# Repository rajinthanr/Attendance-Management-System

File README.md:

# Card Attendance System

A battery-powered NFC attendance logger. A student taps an ID card and the unit
confirms the tap with an LED and a vibration pulse, and stores the card number
with a timestamp in on-chip flash. Plugged into a PC over USB-C, it appears as a
USB drive, with no driver needed.

A desktop companion app for the PC keeps the student names, decides which cards
are registered and works out who attended which lecture.

The repository holds the hardware (KiCad 10), the firmware (STM32CubeIDE /
Makefile), the companion app (Python, Qt) and a 3D-printable enclosure.

## Install the companion app on Windows

1. Download the installer:
   [`Companion/dist/AttendanceLogger-Setup-1.0.0.exe`](Companion/dist/AttendanceLogger-Setup-1.0.0.exe)
   ([direct download](https://github.com/rajinthanr/attendance-management-system/raw/main/Companion/dist/AttendanceLogger-Setup-1.0.0.exe), 26 MB).
2. Run it. It installs for the current user without an admin prompt (it offers
   an all-users install too), into `%LOCALAPPDATA%\Programs\Attendance Logger`.
   Python and Qt are bundled, so nothing else needs installing.
3. Start **Attendance Logger** from the Start menu (or the optional desktop
   icon). **Attendance Logger (demo, made-up data)** shows the whole app without
   a device.

- **Requirements:** 64-bit Windows 10 or 11.
- **"Windows protected your PC":** the installer is not code-signed, so
  SmartScreen may warn the first time. Choose *More info*, then *Run anyway*.
- **Your data** lives in `%USERPROFILE%\AttendanceLogger\attendance.db`, with a
  daily backup in `backups\` (the last 14 kept). Uninstalling or upgrading the
  app leaves it in place.
- **Upgrading:** run a newer installer over the old one.

On Linux, build the `.deb` or a portable `.tar.gz` with
`sh Companion/packaging/build_linux.sh`; on macOS, or to run from source, see
[Running from source](#running-from-source). [`Companion/README.md`](Companion/README.md)
explains the app in full.

## Project status (2026-10-14)

| Area | State |
|---|---|
| Schematic and PCB | Routed except the NFC antenna loop (AE3), which still has to be placed and its feed routed. The through-hole parts (battery connector, SWD header, NTC) moved to the back on 2026-10-11 for the slim enclosure, so `PCB/production/` and `PCB/bom/` need regenerating. |
| Firmware | Runs on the board. Card reading, the reader's low-power card wake-up, LEDs, vibration, Stop 2 sleep and the USB drive work. 931 host checks pass. |
| Companion app | Qt desktop app with Windows and Linux installers, built by GitHub Actions on every change. |
| Enclosure | Two-part printed case (base and lid), designed in code and fit-checked against the board. |

## How it works

1. **Card tap.** The ST25R3916 reader sleeps in its own wake-up mode, watching
   the antenna for a card, and wakes the MCU when one comes near. It reads
   ISO14443-A cards (MIFARE Classic, NTAG and similar). The card number is the
   UID: 4-byte UIDs as they are, longer ones by their last four bytes.
2. **Check.** A card read again within 10 s, or already recorded in the current
   lecture, is a duplicate and is not recorded again. Every other card is
   recorded. The device keeps no list of students: it records every card, and
   the PC app decides who is registered.
3. **Feedback.**

   | Result | Feedback |
   |---|---|
   | Tap recorded | green LED and one short buzz |
   | Duplicate | green flashes twice, with a short buzz each |
   | New lecture started (button hold) | green and three quick buzzes |
   | Battery low | red blinks five times (and the idle flash turns red) |
   | Log full, or reader fault | red flashes four times, with a buzz each |
   | Settings applied / refused | green and two buzzes / red and three buzzes |
   | Waiting for cards | a 10 ms green flash every 5 s (red when the battery is low) |
   | Plugged into a computer | a green flash every second |

4. **Logging.** Taps go to a RAM buffer, then to flash within 5 seconds. The log
   holds 6,858 records and survives a power cut. When it is full, new taps are
   refused rather than overwriting old ones.
5. **Lectures.** Starting a lecture writes a marker into the log, so taps are
   grouped by lecture even without the app. A lecture is started from the app,
   or on the device by holding the button for 2 s (it keeps the module and
   numbers the lecture on: *Lecture 4* becomes *Lecture 5*). A card counts once
   per lecture. The app imports every tap before a lecture starts and then has
   the device delete its copy (`#CLEARLOG`).
6. **USB.** Plug in USB-C and the device appears as a drive called
   **ATTENDANCE**. A tap while it is plugged in is not attendance: it goes to
   `LASTCARD.TXT`, so the app can register the card. Ejecting the drive or
   tapping the button applies `SETTINGS.CSV` and starts taking attendance with
   the cable still in; a quick double press brings the drive back. A USB
   charger that is not a computer is recognised after 5 s, and scanning carries
   on while it charges.
7. **Power.** Press the button to switch on; a tap shows the battery level.
   Holding it for 5 s switches the device off. On battery it switches itself off
   after 3 minutes without a tap, or when the battery is flat.

[`Firmware/docs/Attendance_Logger_Easy_Guide.pdf`](Firmware/docs/Attendance_Logger_Easy_Guide.pdf)
is a five-page, picture-led guide to hand to lecturers;
[`Firmware/docs/USER_GUIDE.md`](Firmware/docs/USER_GUIDE.md) explains the device
in full for the people who run a class with it.

## Low power: measured

The logger spends almost all of its life in one of two low-power states, and
draws large currents only for milliseconds per tap. **One charge of a 1000 mAh
cell lasts about 17 months** at four 100-student lectures a day (27 months from
the device's own draw; the rest is the cell's self-discharge).

| State | Current (measured) | What is running |
|---|---|---|
| Switched off | **1.8 µA** | MCU in Standby with the RTC, reader powered down |
| Switched on, waiting for cards | **108 µA** | MCU in Stop 2, reader in its own wake-up mode, 10 ms heartbeat flash every 5 s |
| Reading a card | 202 mA for 12.2 ms | RF field on: REQA, anticollision, SELECT |
| Buzz | 91 mA for 50 ms | vibration motor starting and running |
| One whole tap | **10.3 mC (2.8 µAh)** | read, buzz and the LED pattern |
| One 100-student lecture | 0.36 mAh | 100 taps plus the idle time |
| For comparison: plain polling | 18.9 mA | reader polled every 100 ms instead of wake-up mode; 2 days per charge |

The trick is the reader's wake-up mode. Instead of the MCU switching the
13.56 MHz field on every 100 ms to look for a card (18.9 mA on average), the
ST25R3916 measures its antenna by itself for about 0.7 ms every 100 ms and
interrupts the MCU only when the reading changes. That is 175 times less
current, and 91 % of what is left:

### Oscilloscope captures

Measured on 8 October 2026 with a Tektronix TBS1052C across a 1 Ω shunt in the
battery's negative lead (1 mV = 1 mA), each capture's offset removed. Steady
currents (Standby, Stop 2, reader Ready) were read with a multimeter in series
with the cell, using a power-test build that holds each load steady.

**One wake-up measurement.** The reader's oscillator starts, the antenna is
driven for 41 µs, and everything stops again: 9.9 µC, ten times a second, is
99 µA on average.

**A card tap.** The measurement that sees the card wakes the MCU, which switches
the field on to read the card (202 mA for 12.2 ms), then buzzes the motor and
lights the green LED with the field off.

**A false wake-up.** When the antenna reading strays without a card, one empty
poll (5.7 ms) confirms it and the reader goes straight back to wake-up mode.
The firmware learns from these and widens its window, so they stay rare.

The raw captures are `Waveforms/TEK0000{5,6,7}.CSV`; `python3 Waveforms/readme_plots.py`
redraws these graphs, and [`Firmware/docs/Power_Estimation_Report.pdf`](Firmware/docs/Power_Estimation_Report.pdf)
has the full analysis (every mode, wake-up timings, battery life and the cost
of the unit).

### Files on the USB drive

| File | Contents |
|---|---|
| `ATTEND.CSV` | every tap (`DATE,TIME,CARD_ID`), read-only |
| `LECTURES.CSV` | every lecture start (date, time, module, lecture), read-only |
| `LECTURES\` | one read-only CSV per lecture, e.g. `L001_2026-10-07_14-30.csv` |
| `STATUS.TXT` | device ID, clock, battery, record count, current lecture |
| `LASTCARD.TXT` | the card last tapped while plugged in, for registering it |
| `SETTINGS.CSV` | edited by the PC: set the clock (`#TIME`), start a lecture (`#MODULE`, `#LECTURE`, `#NEWSESSION`), clear the log (`#CLEARLOG`), set the device ID (`#DEVICE`) |

## Hardware

| Function | Part | Notes |
|---|---|---|
| MCU | STM32L432**KB** (Cortex-M4F, 128 kB flash, 64 kB RAM, QFN-32) | Runs at 4 MHz from MSI, and 24 MHz during USB sessions, with a 32.768 kHz LSE crystal; sleeps in Stop 2 when idle. The 128 kB of flash holds both the firmware (72 kB) and the attendance log (56 kB). |
| NFC reader | ST25R3916 (13.56 MHz, QFN-32) on SPI1 | Differential antenna drive with an EMC filter, a matching network and a capacitive RX divider; 27.12 MHz crystal. |
| Antenna | PCB loop, `NFC_Loop_40x30_3T` (40 × 30 mm, 3 turns) | In the keep-out area at the top of the board. |
| Backup reader | 8-pin header for a PN532 breakout (Elechouse V3 SPI pinout) | Shares SPI1, with its own chip-select (PA15) and IRQ (PB6). Not fitted, and not used by the firmware yet. |
| Charger | MCP73833 Li-ion linear charger | 10 kΩ NTC and three charge-status LEDs. |
| 3.3 V rail | TPS7A0233 LDO, 200 mA | Runs from the cell. The reader's VDD/VDD_TX come straight from the battery, and its VDD_IO from 3.3 V. |
| USB | USB-C receptacle (GCT USB4110), USB 2.0 full speed | Sink-only with 5.1 kΩ CC resistors; USBLC6-2SC6 ESD protection. |
| Battery | Single-cell Li-ion, 3.7 V, 2-pin JST | Sensed through a 4.7 MΩ / 2.7 MΩ divider with 100 nF, on the ADC (PA7) and the PVD input (PB7). |
| Feedback | Red and green LEDs, vibration motor | The motor is switched by an AO3400A MOSFET with an SS14 flyback diode. |
| Buttons | Power (PA0 / WKUP1), reset, BOOT0 | |
| Debug | 4-pin SWD header: 3V3, SWDIO, SWCLK, GND | |

### MCU pin map

| Pin | Signal | Pin | Signal |
|---|---|---|---|
| PA0 | Power button (EXTI0, WKUP1) | PB0 | ST25R3916 chip-select |
| PA2 / PA3 | Green / red LED | PB1 | ST25R3916 IRQ (EXTI1, card wake-up) |
| PA4 | Vibration motor enable | PB3 / PB4 / PB5 | SPI1 SCK / MISO / MOSI |
| PA7 | Battery sense (ADC1_IN12) | PB6 | PN532 IRQ |
| PA9 | VBUS detect (EXTI9) | PB7 | Battery sense (external PVD input) |
| PA11 / PA12 | USB D- / D+ | PA15 | PN532 chip-select |
| PA13 / PA14 | SWDIO / SWCLK | PC14 / PC15 | 32.768 kHz crystal |

`Firmware/Bsp/Inc/bsp_board.h` is the firmware's reference for the pin map, and
`Firmware/Card Attendance System.ioc` for the CubeMX configuration.

### PCB

- **Board:** 60 × 88.6 mm, 2 layers, 1.6 mm FR-4. SMD parts on the top; the
  through-hole battery connector, SWD header and NTC on the back, so the front
  stays flat.
- **Floorplan:** the NFC antenna fills the top of the board. Below it are the
  PN532 header, the MCU and the ST25R3916 front end. The power section (USB-C,
  ESD, charger, LDO, battery connector) runs along the bottom edge.
- **Schematic sheets:**
  - `power.kicad_sch`: USB-C, ESD, charger, LDO and battery.
  - `mcu.kicad_sch`: STM32, buttons, LEDs, motor driver, SWD and the PN532
    header.
  - `rfid.kicad_sch`: ST25R3916, crystal, EMC filter, matching network and
    antenna.
- **Rules:** manufacturing rules are in `PCB/Attendance Management System.kicad_dru`.
  The production files sent to JLCPCB are in `PCB/production/`.

### Enclosure

`Enclosure/` holds a slim two-part case, 18.8 mm tall: a flat lid with LED
light pipes and a flush flexure power button, and a base that clamps the battery
and motor under the board. Both parts print without supports and are also
designed to be mouldable. `enclosure.py` generates the STL files in
`Enclosure/stl/` from the board file and checks the fit; `view.py` is an
interactive section viewer. See [`Enclosure/README.md`](Enclosure/README.md).

## Firmware

The firmware is split along one rule: **the application logic (`App/`) decides,
the drivers (`Bsp/`) act.**

- **`App/`:** the state machine, ISO14443-A protocol, card presence tracking,
  button debouncing, flash log and device config, lecture sessions, the
  `SETTINGS.CSV` parser, the FAT12 volume, CSV and status files, and battery
  maths. It includes no HAL or register headers and compiles on a PC.
- **`Bsp/`:** implements the hardware contract in `App/Inc/platform_if.h`,
  handing up only raw values. It includes the register-level ST25R3916 driver
  (`bsp_nfc.c`).
- **`Tests/`:** builds all of `App/` against a RAM-backed stub platform with a
  simulated card and a simulated PC editing the drive, so the logic is tested
  without hardware.

The main loop handles events, then sleeps until the next deadline: in Stop 2
when idle, woken by LPTIM1, the button, VBUS or the reader's card wake-up.
[`Firmware/docs/ARCHITECTURE.md`](Firmware/docs/ARCHITECTURE.md) describes the
whole design: the flash layout, record, CSV and settings formats, sessions, the
USB volume, power, and known limitations.

For debugging, `dbg_*` globals defined in `Core/Src/main.c` show the battery
voltage, the last card, button presses, reader status and record counts in
STM32CubeIDE's Live Expressions view.

### Build and test

Run these from `Firmware/`:

```sh
make test    # host tests for the application logic; needs only a native C compiler
make         # cross-compiles build/card-attendance.{elf,hex,bin}
make clean
```

- **Toolchain:** `make` uses the GCC bundled with STM32CubeIDE
  (`/opt/st/stm32cubeide_*`) when one is installed, and otherwise
  `arm-none-eabi-gcc` on `PATH`.
- **Flashing and debugging:** use STM32CubeIDE over the SWD header.
- **Optional:** `Tests/fs_check.sh` checks the USB volume with real FAT tools
  (needs `mtools` and `dosfstools`).

### Data on the device

- **Flash layout:** the firmware takes the first 72 kB of the 128 kB flash; the
  last 56 kB (from `0x08012000`) is reserved for data by the linker script.
  - Its first page: configuration (device ID).
  - The other 27 pages: the attendance log, 6,858 records.
- **Records:** each record is 8 bytes (card number and seconds since
  2000-01-01), exactly one flash double-word. Lecture markers are records with
  reserved IDs from `0xFFFFFF00` up.
- **Setting up a device:** nothing is needed for it to log. The clock starts from
  the firmware's build time until it is set with `#TIME` in `SETTINGS.CSV` (the
  companion app does this when you start a lecture, or with *Set device time*).

## Companion app

`Companion/` is a desktop app for the PC the device is plugged into. It runs
entirely on that computer, with no internet. It finds the device, reads its taps
into a local SQLite database, keeps student names and cards (register a card by
tapping it on the plugged-in device), starts lectures, shows the device's
battery, and saves attendance lists as CSV or PDF.

### Installers

| Platform | Get it | Build it yourself |
|---|---|---|
| Windows | [`Companion/dist/AttendanceLogger-Setup-1.0.0.exe`](Companion/dist/AttendanceLogger-Setup-1.0.0.exe) (see [above](#install-the-companion-app-on-windows)) | `Companion\packaging\build_windows.bat` on Windows (Python 3 and Inno Setup 6), or `sh Companion/packaging/build_windows_docker.sh` from Linux (Docker) |
| Linux | build it, or download from GitHub Actions | `sh Companion/packaging/build_linux.sh`: a `.deb` (`sudo apt install ./attendance-logger_*.deb`) and a portable `.tar.gz` |

GitHub Actions (`.github/workflows/companion-installers.yml`) builds both
whenever `Companion/` changes; the files are under the run's *Artifacts* on the
Actions tab. Pushing a tag such as `companion-v1.2.0` builds that version and
attaches the installers to a GitHub release. Builds land in `Companion/dist/`;
only the Windows `.exe` is committed.

### Running from source

Needs Python 3.8 or newer. From `Companion/`:

```sh
python -m venv .venv
.venv/bin/pip install -r requirements.txt     # Windows: .venv\Scripts\pip install -r requirements.txt
sh start.sh                                   # Windows: start.bat
python attendance_qt.py --demo                # made-up data, no device needed
```

## Repository layout

```
Firmware/            STM32CubeIDE project + standalone Makefile
  App/               application logic (portable, host-tested)
  Bsp/               board support: HAL drivers, ST25R3916 driver, USB MSC glue
  Core/              CubeMX-generated startup code (edit only inside USER CODE blocks)
  Drivers/           ST HAL and CMSIS
  Middlewares/       ST USB Device Library (core + MSC)
  Tests/             host test harness and tools
  docs/              ARCHITECTURE.md (design), USER_GUIDE.md (for users)
  Card Attendance System.ioc   CubeMX pin and peripheral configuration
Companion/           PC app (Python, Qt): window, database, reports
  dist/              Windows installer (AttendanceLogger-Setup-<version>.exe)
  packaging/         PyInstaller spec, Inno Setup script, installer build scripts
PCB/                 KiCad 10 project, BOMs (bom/) and JLCPCB production files (production/)
Enclosure/           3D-printable enclosure (enclosure.py, STL files in stl/)
LICENSE              MIT
```

## Tools

- **PCB:** KiCad 10.0.
- **Firmware:** STM32CubeIDE 1.19 (CubeMX 6.15, STM32Cube FW_L4 V1.18.2), or
  `arm-none-eabi-gcc` with `make`.
- **Host tests:** any C11 compiler (`cc`).
- **Companion app:** Python 3.8+ with PySide6 (Qt), or none with the installer.
- **Enclosure:** Python with `manifold3d` (and `pyvista` for the viewer).

## Known issues

- **External footprint library.** Some footprints come from a SnapEDA library at
  an absolute path outside the repository, so a fresh clone can't resolve them
  until the library is added or the paths are updated.

## License

MIT. See [LICENSE](LICENSE).

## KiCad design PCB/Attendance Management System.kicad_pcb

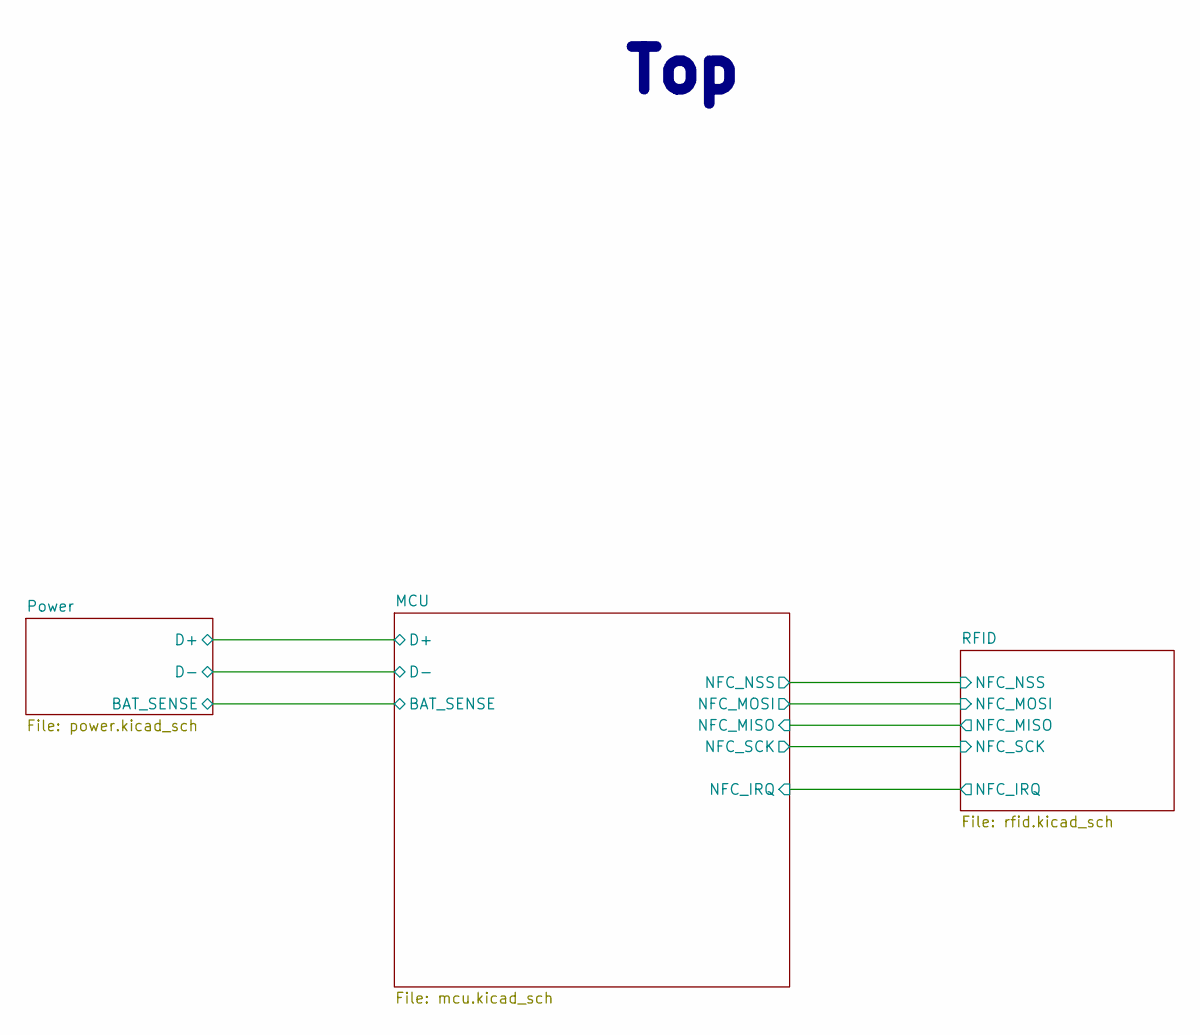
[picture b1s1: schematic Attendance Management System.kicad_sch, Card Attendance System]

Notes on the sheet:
Top

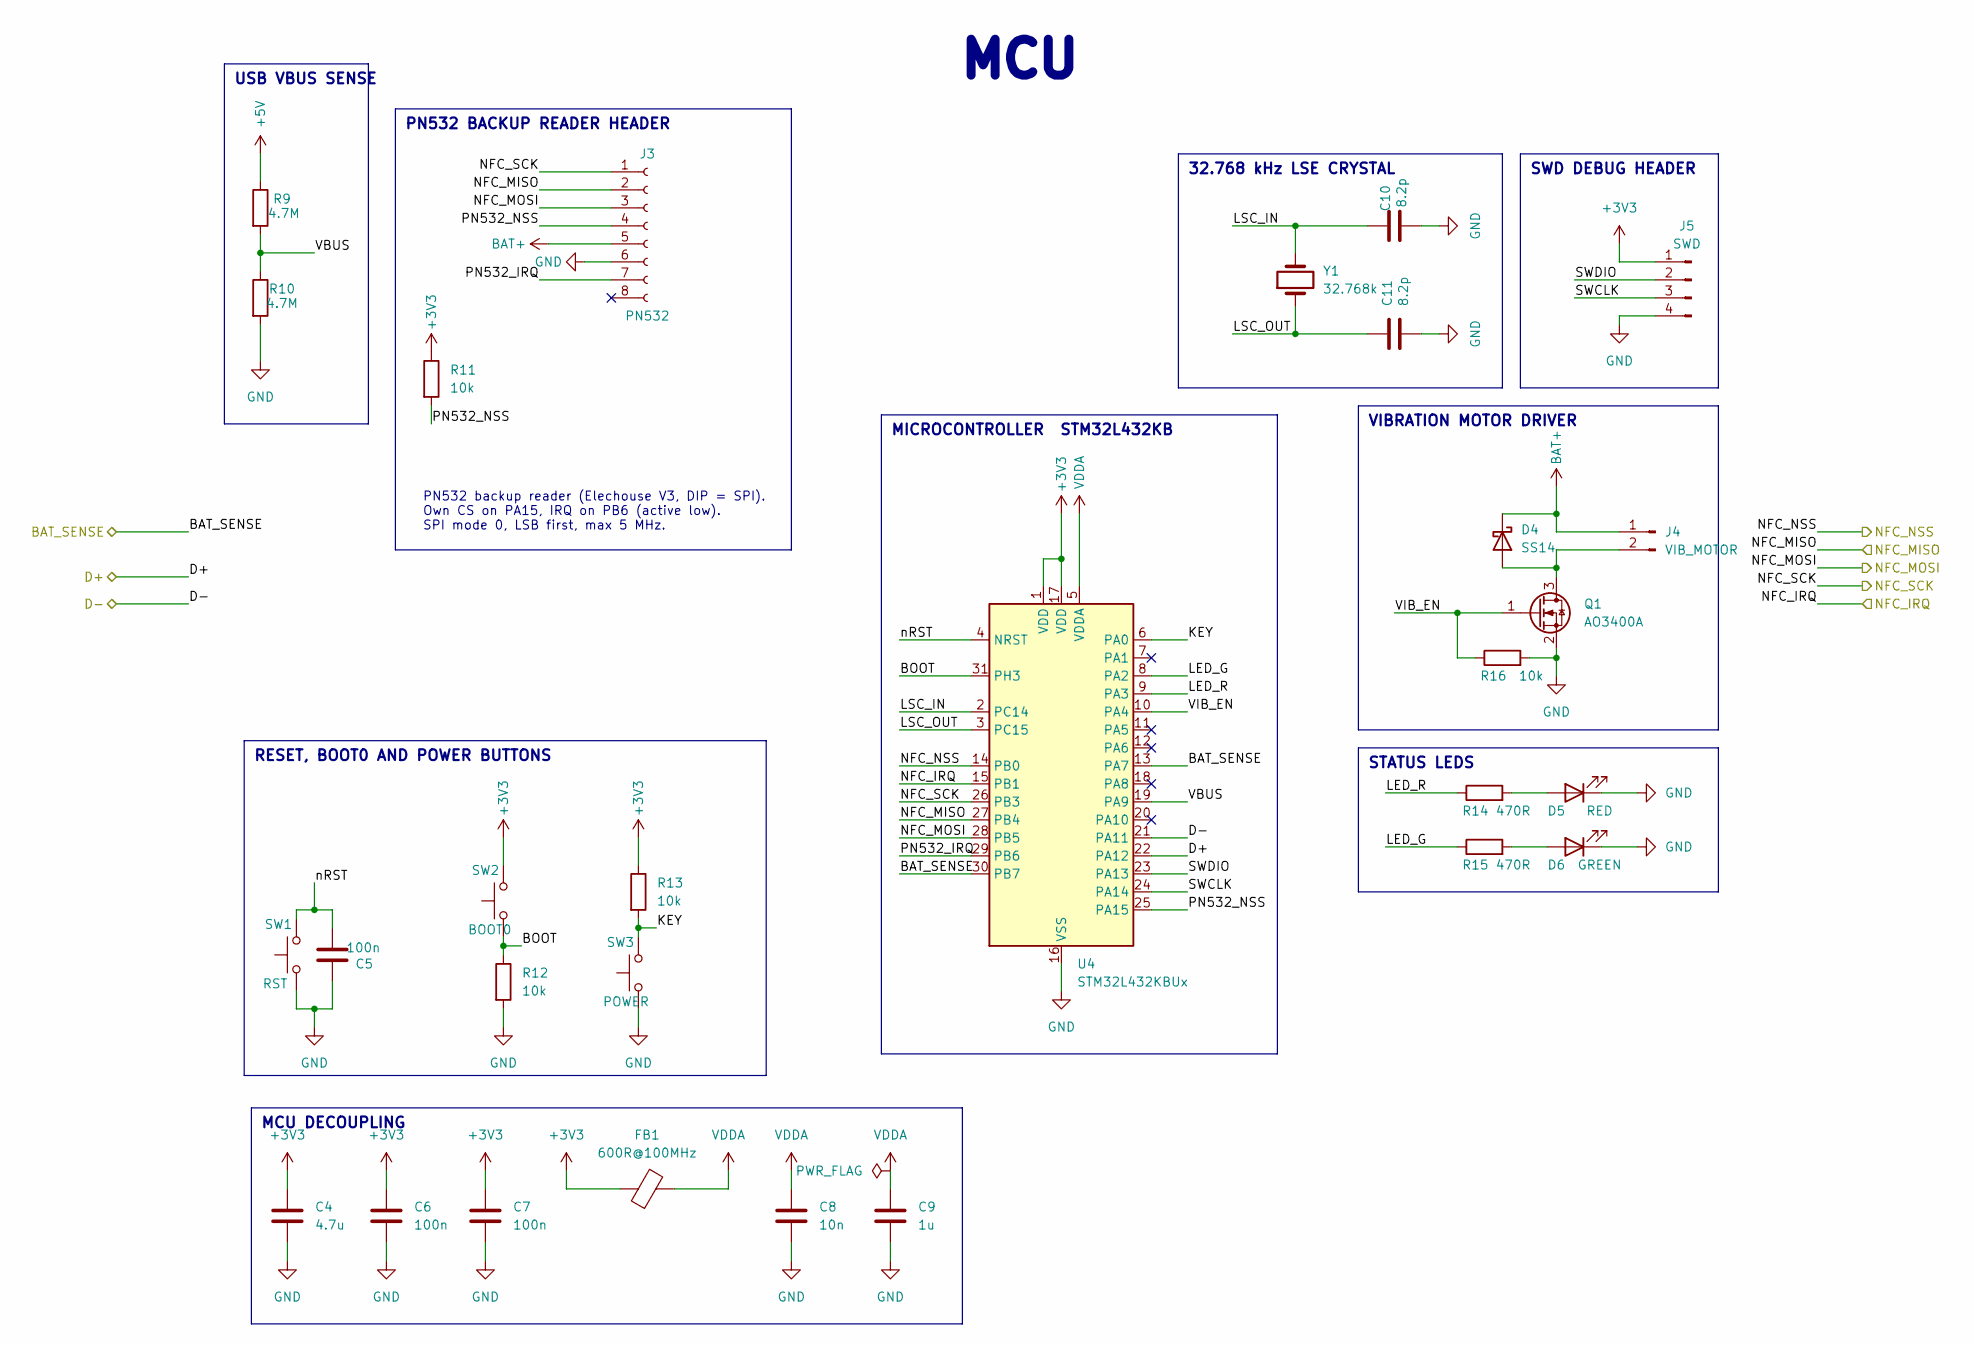
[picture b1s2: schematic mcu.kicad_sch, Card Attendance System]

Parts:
C4: 4.7u; C_0805_2012Metric; Voltage 10V; LCSC C1779
C5, C6, C7: 100n; C_0805_2012Metric; Voltage 16V; LCSC C49678
C8: 10n; C_0805_2012Metric; Voltage 16V; LCSC C1710
C9: 1u; C_0805_2012Metric; Voltage 10V; LCSC C28323
C10, C11: 8.2p; C_0805_2012Metric; Voltage 50V; LCSC C1840
D4: SS14; D_SMA; LCSC C2480
D5: RED; LED_0805_2012Metric; LCSC C84256
D6: GREEN; LED_0805_2012Metric; LCSC C98221
FB1: 600R@100MHz; L_0402_1005Metric; LCSC C76884
J3: PN532; PinSocket_1x08_P2.54mm_Vertical; LCSC C42431840
J4: VIB_MOTOR; PinHeader_1x02_P2.54mm_Vertical; LCSC C492401
J5: SWD; PinHeader_1x04_P2.54mm_Vertical; LCSC C2691448
Q1: AO3400A; SOT-23; LCSC C20917
R9, R10: 4.7M; R_0805_2012Metric; LCSC C17674
R11, R12, R13, R16: 10k; R_0805_2012Metric; LCSC C17414
R14, R15: 470R; R_0805_2012Metric; LCSC C17710
SW1: RST; SW_Tactile_SPST_NO_Straight_CK_PTS636Sx25SMTRLFS; LCSC C2689642
SW2: BOOT0; SW_Tactile_SPST_NO_Straight_CK_PTS636Sx25SMTRLFS; LCSC C2689642
SW3: POWER; SW_Tactile_SPST_NO_Straight_CK_PTS636Sx25SMTRLFS; LCSC C2689642
U4: STM32L432KBUx; QFN-32-1EP_5x5mm_P0.5mm_EP3.45x3.45mm; LCSC C2928224
Y1: 32.768k; Crystal_SMD_EuroQuartz_EQ161-2Pin_3.2x1.5mm; LCSC C95361

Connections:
+3V3: C4.1, C6.1, C7.1, FB1.1, J5.1, R11.1, R13.1, SW2.2, U4.1 (VDD), U4.17 (VDD); also elsewhere on the board
+5V: R9.1; also elsewhere on the board
/MCU/BAT_SENSE: U4.13 (PA7), U4.30 (PB7); also elsewhere on the board
/MCU/BOOT: R12.1, SW2.1, U4.31 (PH3)
/MCU/D+: U4.22 (PA12); also elsewhere on the board
/MCU/D-: U4.21 (PA11); also elsewhere on the board
/MCU/KEY: R13.2, SW3.2, U4.6 (PA0)
/MCU/LED_G: R15.1, U4.8 (PA2)
/MCU/LED_R: R14.1, U4.9 (PA3)
/MCU/LSC_IN: C10.2, U4.2 (PC14), Y1.2
/MCU/LSC_OUT: C11.1, U4.3 (PC15), Y1.1
/MCU/NFC_IRQ: U4.15 (PB1); also elsewhere on the board
/MCU/NFC_MISO: J3.2, U4.27 (PB4); also elsewhere on the board
/MCU/NFC_MOSI: J3.3, U4.28 (PB5); also elsewhere on the board
/MCU/NFC_NSS: U4.14 (PB0); also elsewhere on the board
/MCU/NFC_SCK: J3.1, U4.26 (PB3); also elsewhere on the board
/MCU/PN532_IRQ: J3.7, U4.29 (PB6)
/MCU/PN532_NSS: J3.4, R11.2, U4.25 (PA15)
/MCU/SWCLK: J5.3, U4.24 (PA14)
/MCU/SWDIO: J5.2, U4.23 (PA13)
/MCU/VBUS: R9.2, R10.1, U4.19 (PA9)
/MCU/VIB_EN: Q1.1 (G), R16.1, U4.10 (PA4)
/MCU/nRST: C5.1, SW1.2, U4.4 (NRST)
BAT+: D4.1 (K), J3.5, J4.1; also elsewhere on the board
GND: C4.2, C5.2, C6.2, C7.2, C8.2, C9.2, C10.1, C11.2, D5.1 (K), D6.1 (K), J3.6, J5.4, Q1.2 (S), R10.2, R12.2, R16.2, SW1.1, SW3.1, U4.16 (VSS), U4.32 (VSS), U4.33 (VSS); also elsewhere on the board
unnamed: D4.2 (A), J4.2, Q1.3 (D)
unnamed: D5.2 (A), R14.2
unnamed: D6.2 (A), R15.2
VDDA: C8.1, C9.1, FB1.2, U4.5 (VDDA)

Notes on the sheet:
PN532 backup reader (Elechouse V3, DIP = SPI). Own CS on PA15, IRQ on PB6 (active low). SPI mode 0, LSB first, max 5 MHz.
SWD DEBUG HEADER
VIBRATION MOTOR DRIVER
RESET, BOOT0 AND POWER BUTTONS
MICROCONTROLLER STM32L432KB
MCU
32.768 kHz LSE CRYSTAL
PN532 BACKUP READER HEADER
USB VBUS SENSE
MCU DECOUPLING
STATUS LEDS

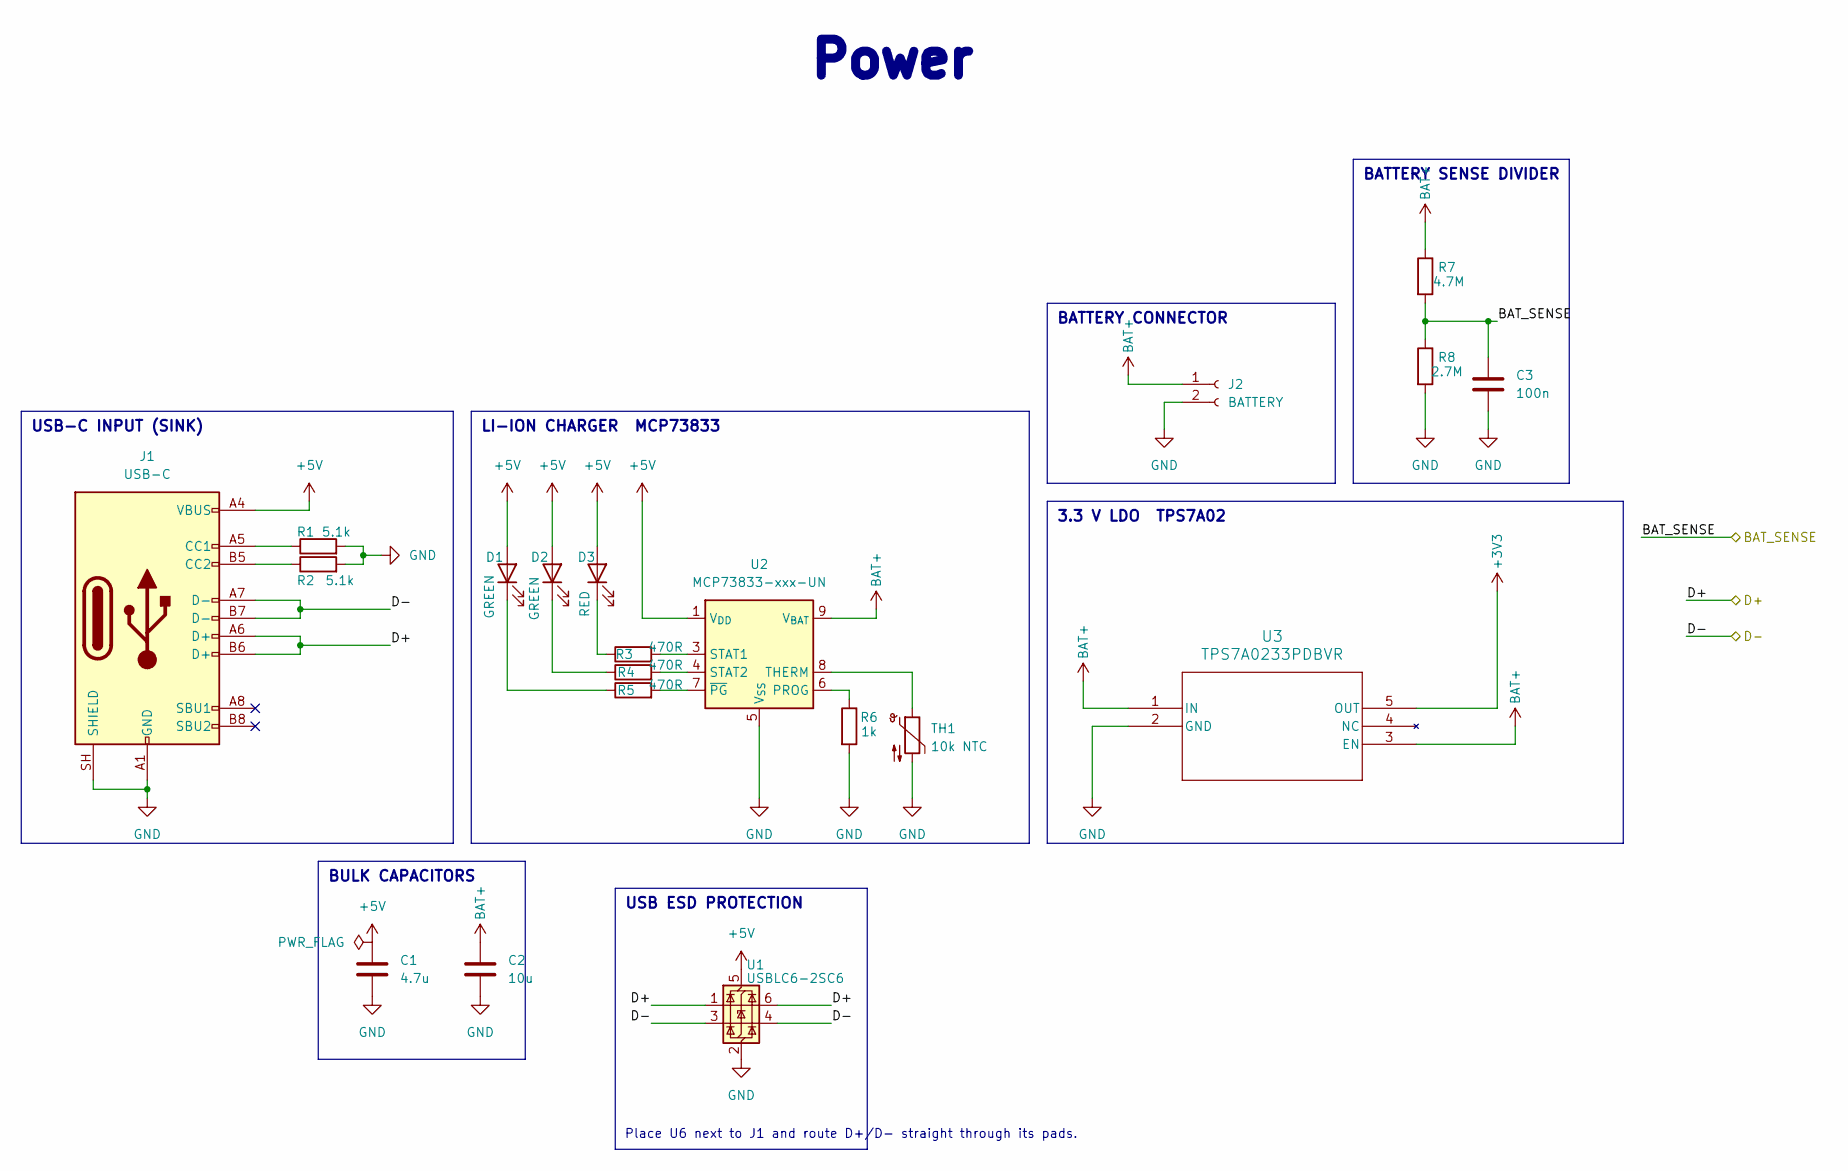
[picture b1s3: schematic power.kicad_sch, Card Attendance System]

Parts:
C1: 4.7u; C_0805_2012Metric; Voltage 16V; LCSC C1779
C2: 10u; C_0805_2012Metric; Voltage 10V; LCSC C15850
C3: 100n; C_0805_2012Metric; Voltage 16V; LCSC C49678
D1, D2: GREEN; LED_0805_2012Metric; LCSC C98221
D3: RED; LED_0805_2012Metric; LCSC C84256
J1: USB-C; USB_C_Receptacle_GCT_USB4110; LCSC C5143397
J2: BATTERY; JST_XA_B02B-XASK-1_1x02_P2.50mm_Vertical; LCSC C263753
R1, R2: 5.1k; R_0805_2012Metric; LCSC C27834
R3, R4, R5: 470R; R_0805_2012Metric; LCSC C17710
R6: 1k; R_0805_2012Metric; LCSC C17513
R7: 4.7M; R_0805_2012Metric; LCSC C17674
R8: 2.7M; R_0805_2012Metric; LCSC C17531
TH1: 10k NTC; R_Axial_DIN0204_L3.6mm_D1.6mm_P1.90mm_Vertical; LCSC C141588
U1: USBLC6-2SC6; SOT-23-6; LCSC C7519
U2: MCP73833-xxx-UN; MSOP-10_3x3mm_P0.5mm; LCSC C627668
U3: TPS7A0233PDBVR; SOT23_DBV_TEX-L; LCSC C2887324

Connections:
+3V3: U3.5 (OUT); also elsewhere on the board
+5V: C1.1, D1.2 (A), D2.2 (A), D3.2 (A), J1.A4 (VBUS), J1.A9 (VBUS), J1.B4 (VBUS), J1.B9 (VBUS), U1.5 (VBUS), U2.1 (V_{DD}), U2.2 (V_{DD}); also elsewhere on the board
/MCU/BAT_SENSE: C3.1, R7.2, R8.1; also elsewhere on the board
/MCU/D+: J1.A6 (D+), J1.B6 (D+), U1.1 (I/O1), U1.6 (I/O1); also elsewhere on the board
/MCU/D-: J1.A7 (D-), J1.B7 (D-), U1.3 (I/O2), U1.4 (I/O2); also elsewhere on the board
BAT+: C2.1, J2.1, R7.1, U2.9 (V_{BAT}), U2.10 (V_{BAT}), U3.1 (IN), U3.3 (EN); also elsewhere on the board
GND: C1.2, C2.2, C3.2, J1.A1 (GND), J1.A12 (GND), J1.B1 (GND), J1.B12 (GND), J1.SH (SHIELD), J2.2, R1.2, R2.2, R6.2, R8.2, TH1.2, U1.2 (GND), U2.5 (V_{SS}), U3.2 (GND); also elsewhere on the board
unnamed: D1.1 (K), R5.1
unnamed: D2.1 (K), R4.1
unnamed: D3.1 (K), R3.1
unnamed: J1.A5 (CC1), R1.1
unnamed: J1.B5 (CC2), R2.1
unnamed: R6.1, U2.6 (PROG)
unnamed: R3.2, U2.3 (STAT1)
unnamed: R4.2, U2.4 (STAT2)
unnamed: TH1.1, U2.8 (THERM)
unnamed: R5.2, U2.7 (~PG)

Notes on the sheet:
USB-C INPUT (SINK)
LI-ION CHARGER MCP73833
BATTERY CONNECTOR
USB ESD PROTECTION
Power
BATTERY SENSE DIVIDER
3.3 V LDO TPS7A02
BULK CAPACITORS
Place U6 next to J1 and route D+/D- straight through its pads.

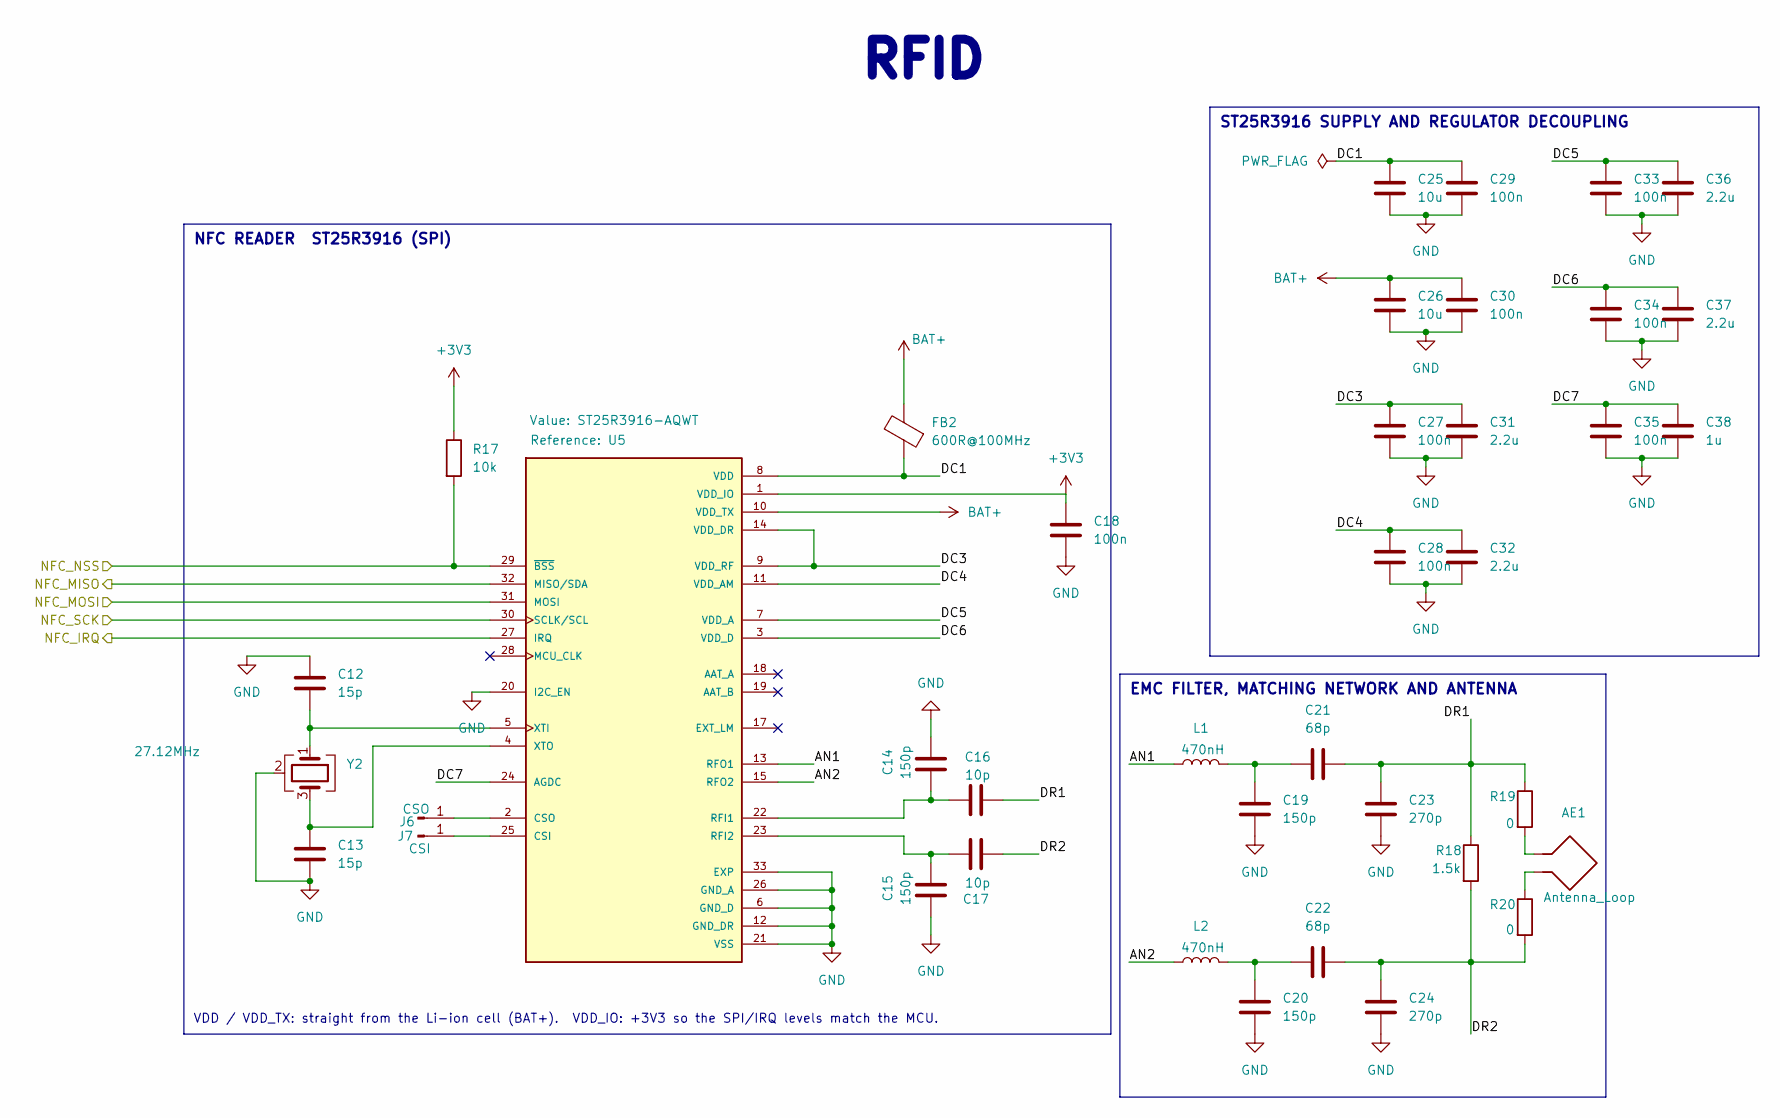
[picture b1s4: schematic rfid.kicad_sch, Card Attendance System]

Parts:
AE1: Antenna_Loop; NFC_Loop_40x30_3T
C12, C13: 15p; C_0805_2012Metric; Voltage 50V; LCSC C107110
C14, C15, C19, C20: 150p; C_0805_2012Metric; Voltage 50V; LCSC C107111
C16, C17: 10p; C_0805_2012Metric; Voltage 50V; LCSC C107107
C18, C27, C28, C29, C30, C33, C34, C35: 100n; C_0805_2012Metric; Voltage 16V; LCSC C49678
C21, C22: 68p; C_0805_2012Metric; Voltage 50V; LCSC C107120
C23, C24: 270p; C_0805_2012Metric; Voltage 50V; LCSC C107106
C25, C26: 10u; C_0805_2012Metric; Voltage 10V; LCSC C15850
C31, C32, C36, C37: 2.2u; C_0805_2012Metric; Voltage 10V; LCSC C377773
C38: 1u; C_0805_2012Metric; Voltage 10V; LCSC C28323
FB2: 600R@100MHz; L_0402_1005Metric; LCSC C76884
J6: CSO; SolderWirePad_1x01_SMD_1x2mm
J7: CSI; SolderWirePad_1x01_SMD_1x2mm
L1, L2: 470nH; L_0805_2012Metric_Pad1.05x1.20mm_HandSolder; LCSC C337959
R17: 10k; R_0805_2012Metric; LCSC C17414
R18: 1.5k; R_0805_2012Metric; LCSC C4310
R19, R20: 0; R_0805_2012Metric; LCSC C17477
U5: ST25R3916-AQWT; QFN50P500X500X100-33N; PARTREV 4; LCSC C2908147
Y2: 27.12MHz; Crystal_SMD_3225-4Pin_3.2x2.5mm_HandSoldering; MPN X32252712MMB4SI; LCSC C29975

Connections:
+3V3: C18.1, R17.1, U5.1 (VDD_IO); also elsewhere on the board
/MCU/NFC_IRQ: U5.27 (IRQ); also elsewhere on the board
/MCU/NFC_MISO: U5.32 (MISO/SDA); also elsewhere on the board
/MCU/NFC_MOSI: U5.31 (MOSI); also elsewhere on the board
/MCU/NFC_NSS: R17.2, U5.29 (~BSS); also elsewhere on the board
/MCU/NFC_SCK: U5.30 (SCLK/SCL); also elsewhere on the board
/RFID/AN1: L1.1, U5.13 (RFO1)
/RFID/AN2: L2.1, U5.15 (RFO2)
/RFID/DC1: C25.1, C29.1, FB2.1, U5.8 (VDD)
/RFID/DC3: C27.1, C31.1, U5.9 (VDD_RF), U5.14 (VDD_DR)
/RFID/DC4: C28.1, C32.1, U5.11 (VDD_AM)
/RFID/DC5: C33.1, C36.1, U5.7 (VDD_A)
/RFID/DC6: C34.1, C37.1, U5.3 (VDD_D)
/RFID/DC7: C35.1, C38.1, U5.24 (AGDC)
/RFID/DR1: C16.1, C21.1, C23.1, R18.1, R19.1
/RFID/DR2: C17.2, C22.1, C24.1, R18.2, R20.2
BAT+: C26.1, C30.1, FB2.2, U5.10 (VDD_TX); also elsewhere on the board
GND: C12.1, C13.2, C14.1, C15.2, C18.2, C19.2, C20.2, C23.2, C24.2, C25.2, C26.2, C27.2, C28.2, C29.2, C30.2, C31.2, C32.2, C33.2, C34.2, C35.2, C36.2, C37.2, C38.2, U5.6 (GND_D), U5.12 (GND_DR), U5.16 (GND_DR), U5.20 (I2C_EN), U5.21 (VSS), U5.26 (GND_A), U5.33 (EXP), Y2.2 (G), Y2.4 (G); also elsewhere on the board
unnamed: AE1.1, R19.2
unnamed: AE1.2, R20.1
unnamed: C19.1, C21.2, L1.2
unnamed: C20.1, C22.2, L2.2
unnamed: J6.1 (Pin_1_1), U5.2 (CSO)
unnamed: J7.1 (Pin_1_1), U5.25 (CSI)
unnamed: C14.2, C16.2, U5.22 (RFI1)
unnamed: C15.1, C17.1, U5.23 (RFI2)
unnamed: C12.2, U5.5 (XTI), Y2.1
unnamed: C13.1, U5.4 (XTO), Y2.3

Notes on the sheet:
VDD / VDD_TX: straight from the Li-ion cell (BAT+). VDD_IO: +3V3 so the SPI/IRQ levels match the MCU.
NFC READER ST25R3916 (SPI)
ST25R3916 SUPPLY AND REGULATOR DECOUPLING
EMC FILTER, MATCHING NETWORK AND ANTENNA
RFID

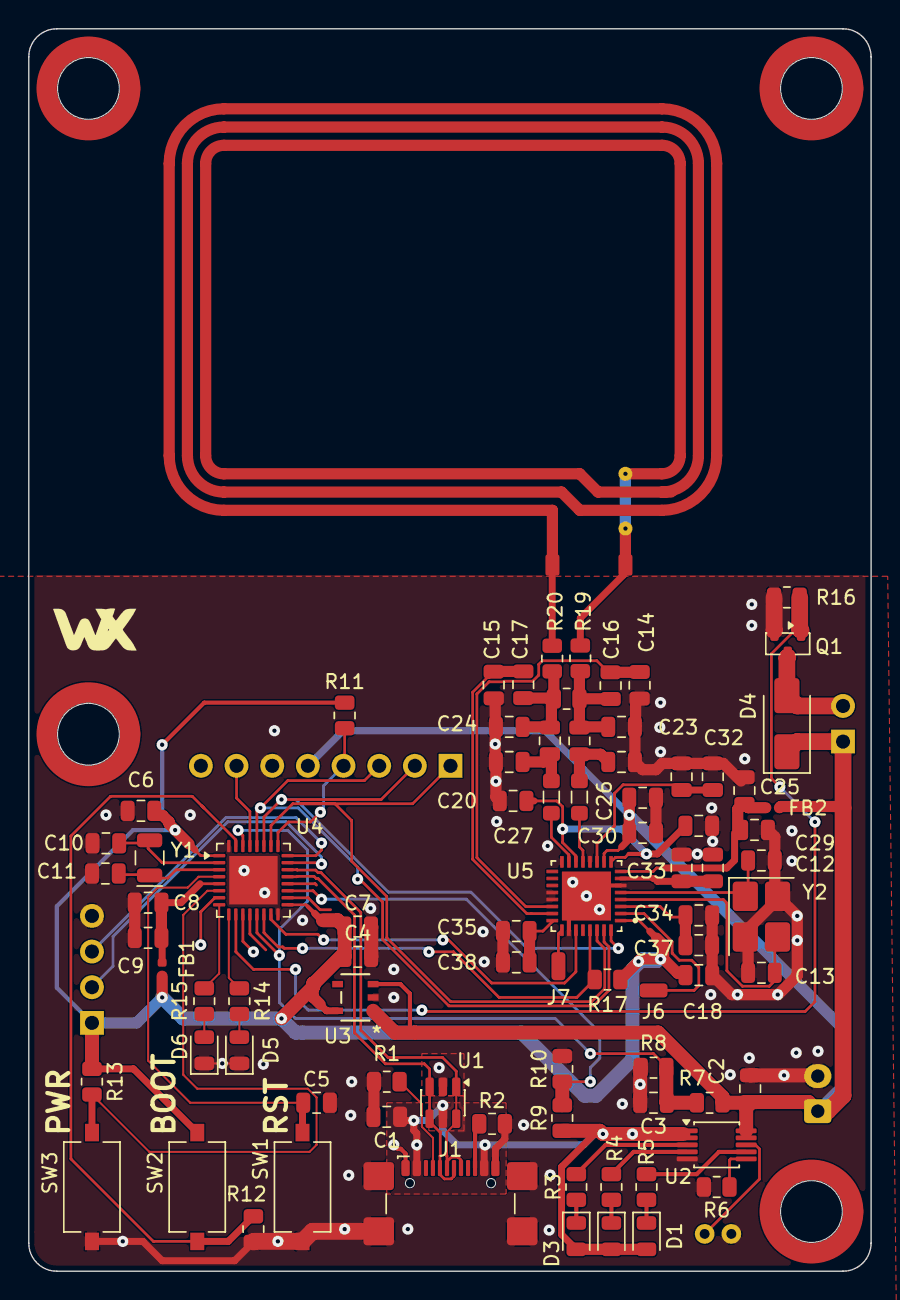
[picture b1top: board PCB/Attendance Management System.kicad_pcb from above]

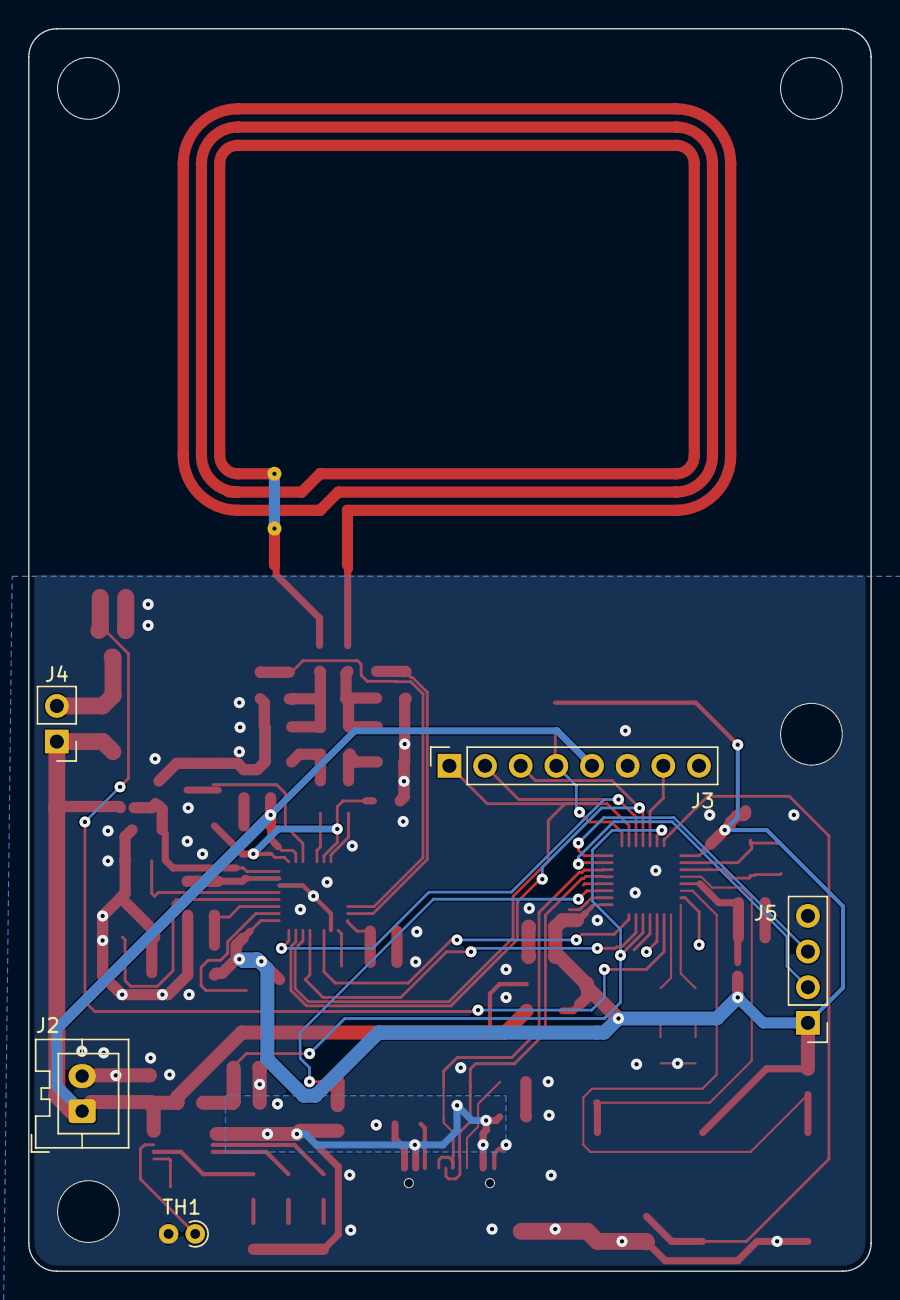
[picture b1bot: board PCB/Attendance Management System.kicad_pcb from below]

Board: 2 copper layers, 60.0 x 88.5 mm, 88 parts (5 on the bottom side), 59 nets.

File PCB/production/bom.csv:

Designator,Footprint,Quantity,Value,LCSC Part #
"C1, C4",0805,2,4.7u,C1779
"C10, C11",0805,2,8.2p,C1840
"C12, C13",0805,2,15p,C107110
"C14, C15, C19, C20",0805,4,150p,C107111
"C16, C17",0805,2,10p,C107107
"C18, C27, C28, C29, C3, C30, C33, C34, C35, C5, C6, C7",0805,12,100n,C49678
"C2, C25, C26",0805,3,10u,C15850
"C21, C22",0805,2,68p,C107120
"C23, C24",0805,2,270p,C107106
"C31, C32, C36, C37",0805,4,2.2u,C377773
"C38, C9",0805,2,1u,C28323
C8,0805,1,10n,C1710
"D1, D2, D6",0805,3,GREEN,C98221
"D3, D5",0805,2,RED,C84256
D4,D_SMA,1,SS14,C2480
"FB1, FB2",0402,2,600R@100MHz,C76884
J1,USB_C_Receptacle_GCT_USB4110,1,USB-C,C5143397
J2,JST_XA_B02B-XASK-1_1x02_P2.50mm_Vertical,1,BATTERY,C263753
J3,PinSocket_1x08_P2.54mm_Vertical,1,PN532,C42431840
J4,PinHeader_1x02_P2.54mm_Vertical,1,VIB_MOTOR,C492401
J5,PinHeader_1x04_P2.54mm_Vertical,1,SWD,C2691448
J6,SolderWirePad_1x01_SMD_1x2mm,1,CSO,
J7,SolderWirePad_1x01_SMD_1x2mm,1,CSI,
"L1, L2",0805,2,470nH,C337959
Q1,SOT-23,1,AO3400A,C20917
"R1, R2",0805,2,5.1k,C27834
"R10, R7, R9",0805,3,4.7M,C17674
"R11, R12, R13, R16, R17",0805,5,10k,C17414
"R14, R15, R3, R4, R5",0805,5,470R,C17710
R18,0805,1,1.5k,C4310
"R19, R20",0805,2,0,C17477
R6,0805,1,1k,C17513
R8,0805,1,2.7M,C17531
SW1,SW_Tactile_SPST_NO_Straight_CK_PTS636Sx25SMTRLFS,1,RST,C2689642
SW2,SW_Tactile_SPST_NO_Straight_CK_PTS636Sx25SMTRLFS,1,BOOT0,C2689642
SW3,SW_Tactile_SPST_NO_Straight_CK_PTS636Sx25SMTRLFS,1,POWER,C2689642
TH1,R_Axial_DIN0204_L3.6mm_D1.6mm_P1.90mm_Vertical,1,10k NTC,C141588
U1,SOT-23-6,1,USBLC6-2SC6,C7519
U2,MSOP-10_3x3mm_P0.5mm,1,MCP73833-xxx-UN,C627668
U3,SOT23_DBV_TEX-L,1,TPS7A0233PDBVR,C2887324
U4,QFN-32-1EP_5x5mm_P0.5mm_EP3.45x3.45mm,1,STM32L432KBUx,C2928224
U5,QFN50P500X500X100-33N,1,ST25R3916-AQWT,C2908147
Y1,Crystal_SMD_EuroQuartz_EQ161-2Pin_3.2x1.5mm,1,32.768k,C95361
Y2,Crystal_SMD_3225-4Pin_3.2x2.5mm_HandSoldering,1,27.12MHz,C29975
